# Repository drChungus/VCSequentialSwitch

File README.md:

# Coupled Sequential Switch
#### Double the switches, double the fun!

The Coupled Sequential Switch (CSS) provides two related sequential switches with four steps.

### Specification:
Width:&nbsp;**4 HP**
Depth:&nbsp;**30 mm**
+12V : **5 mA**
-12V: **0 mA**
5V: **0 mA**

A sequential switch is a device to route your signals to different places. The routing can be controlled with a clock signal or a button on the front panel. A reset input is also available to set the switch to its initial routing. This module combines two switches in a small footprint. The signal paths of the two switches are independent, but their state will always be the same. They can be advanced and reset with the same clock signal resulting in a coupled behavior. 
As both switches are always on the same stage this module is ideal to route dual signals, like stereo audio, CV/Gate pairs, and in general vary two independent signals at the same time. Inputs and outputs for the signal path can be switched up!

For more explanation why a sequential switch might be useful in your rack see [mylarmelodies' video](https://www.youtube.com/watch?v=QbxaWluHXEU) on the topic!

##### Inputs:
- Step
- Reset

##### Bipolar:
- 1x I/O
- 4x O/I

##### UI:
- 4x LEDs to indicate the current stage
- Button to advance stage
- Switch to define the number of stages (4, 3 or 2)

NOTE: there might be some reported issues with the current state of the module. Always see [Issues](https://github.com/drChungus/VCSequentialSwitch/issues) reported!

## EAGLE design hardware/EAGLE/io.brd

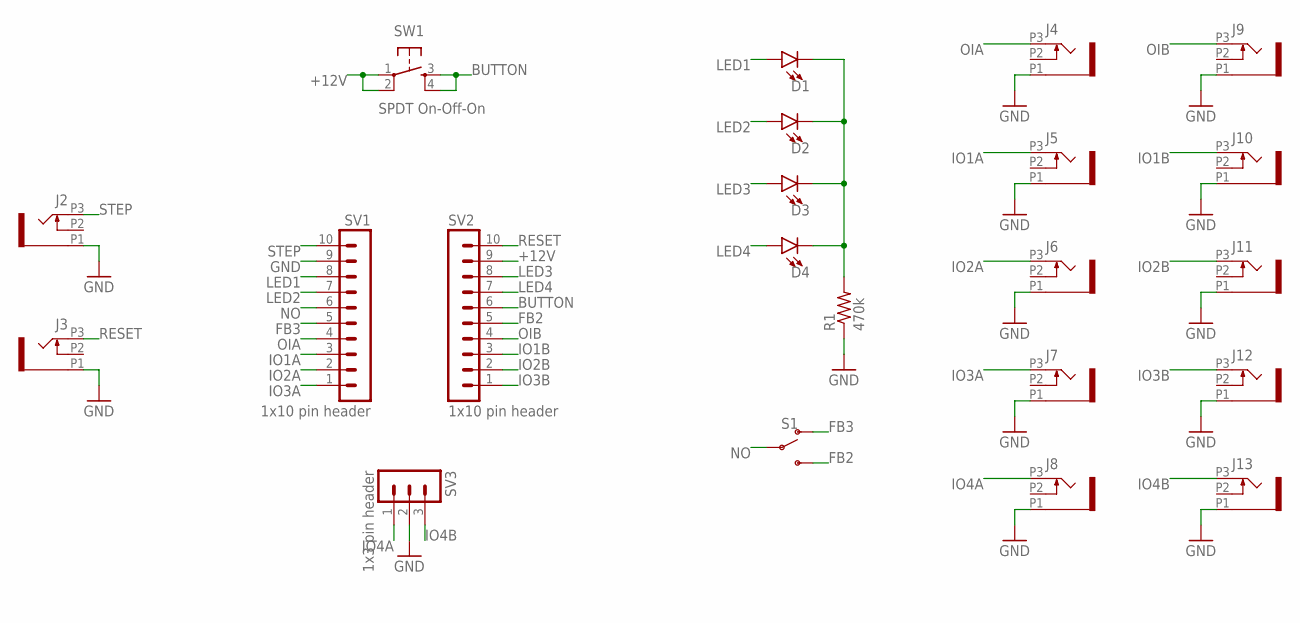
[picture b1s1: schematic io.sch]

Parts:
D1, D2, D3, D4: LED3MM; LED_3MM
J2, J3, J4, J5, J6, J7, J8, J9, J10, J11, J12, J13: PJ301_THONKICONN6; WQP_PJ_301M6
R1: 470k; R0603
S1: SWITCH-SPDT-PTH-11.6X4.0MM-SHORT_LEADS; SWITCH_SPDT_PTH_11.6X4.0MM
SV1, SV2: 1x10 pin header; MA10-1
SV3: 1x3 pin header; MA03-1
SW1: SPDT On-Off-On; TACTILE-PTH

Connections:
+12V: SV2.9, SW1.1, SW1.2
BUTTON: SV2.6, SW1.3, SW1.4
FB2: S1.3 (S), SV2.5
FB3: S1.1 (O), SV1.5
GND: J2.P1 (1), J3.P1 (1), J4.P1 (1), J5.P1 (1), J6.P1 (1), J7.P1 (1), J8.P1 (1), J9.P1 (1), J10.P1 (1), J11.P1 (1), J12.P1 (1), J13.P1 (1), R1.1, SV1.9, SV3.2
IO1A: J5.P3 (3), SV1.3
IO1B: J10.P3 (3), SV2.3
IO2A: J6.P3 (3), SV1.2
IO2B: J11.P3 (3), SV2.2
IO3A: J7.P3 (3), SV1.1
IO3B: J12.P3 (3), SV2.1
IO4A: J8.P3 (3), SV3.1
IO4B: J13.P3 (3), SV3.3
LED1: D1.A, SV1.8
LED2: D2.A, SV1.7
LED3: D3.A, SV2.8
LED4: D4.A, SV2.7
unnamed: D1.K (C), D2.K (C), D3.K (C), D4.K (C), R1.2
NO: S1.2, SV1.6
OIA: J4.P3 (3), SV1.4
OIB: J9.P3 (3), SV2.4
RESET: J3.P3 (3), SV2.10
STEP: J2.P3 (3), SV1.10

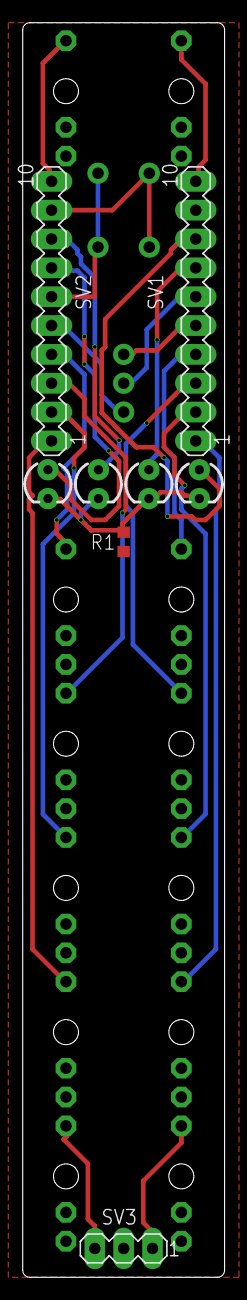
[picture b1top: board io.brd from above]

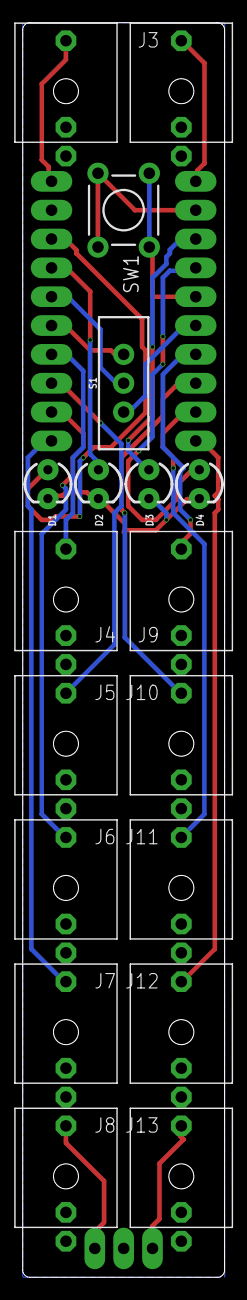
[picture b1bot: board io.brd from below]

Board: 2 copper layers, 17.8 x 110.5 mm, 23 parts (18 on the bottom side), 23 nets.

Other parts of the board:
U$1: EURO_PCB_4HP

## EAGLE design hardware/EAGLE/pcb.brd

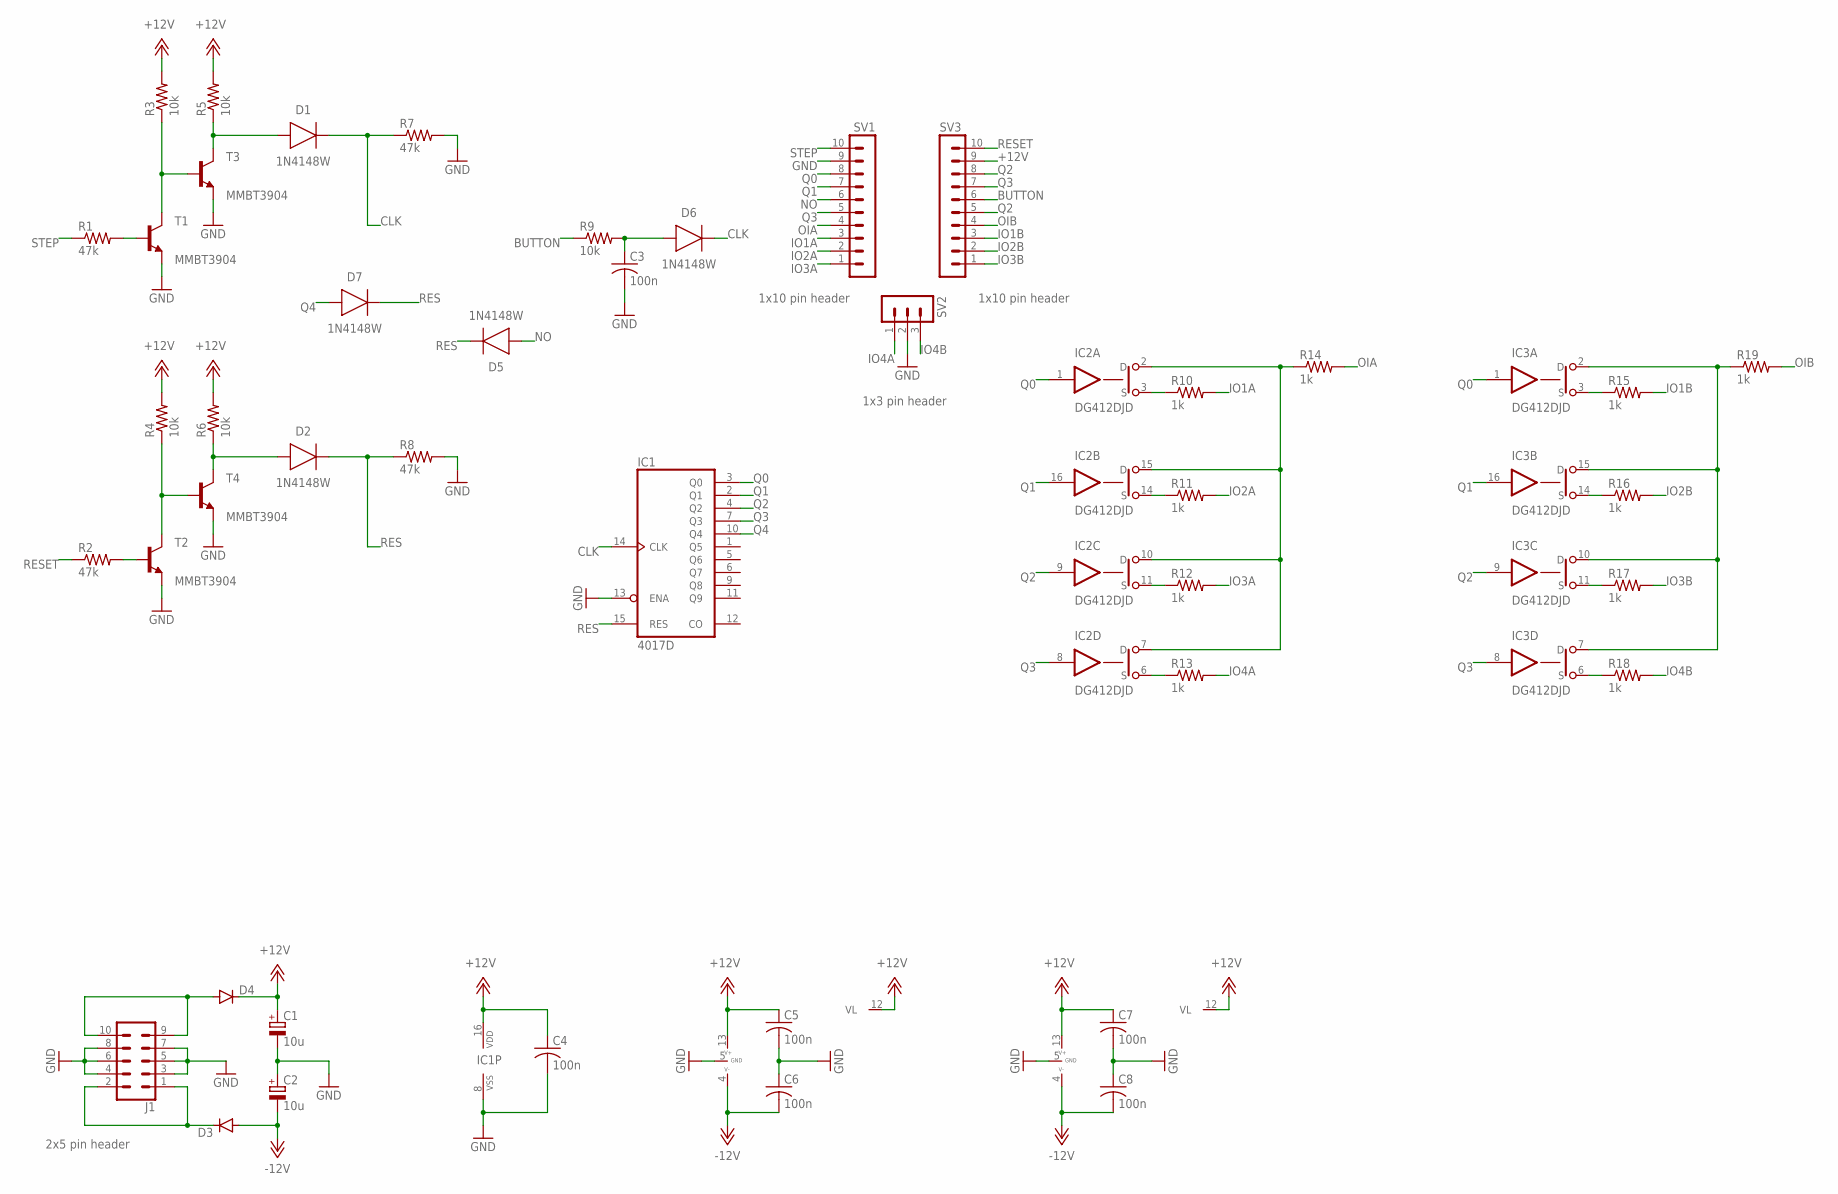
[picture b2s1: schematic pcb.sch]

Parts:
C1, C2: 10u; 153CLV-0605
C3, C4, C5, C6, C7, C8: 100n; C0603
D1, D2, D5, D6, D7: 1N4148W; SOD3715X135
D3, D4: DIODE-SOD123; SOD123
IC1: 4017D; SO16
IC2, IC3: DG412DJD; SO16
J1: 2x5 pin header; 2X5-SHROUDED
R1, R2, R7, R8: 47k; R0603
R3, R4, R5, R6, R9: 10k; R0603
R10, R11, R12, R13, R14, R15, R16, R17, R18, R19: 1k; R0603
SV1, SV3: 1x10 pin header; MA10-1
SV2: 1x3 pin header; MA03-1
T1, T2, T3, T4: MMBT3904; SOT23-BEC

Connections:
+12V: C1.+, C4.1, C5.1, C7.1, D4.C, IC1.16 (VDD), IC2.12 (VL), IC2.13 (V+), IC3.12 (VL), IC3.13 (V+), R3.2, R4.2, R5.2, R6.2, SV3.9
-12V: C2.-, C6.2, C8.2, D3.A, IC2.4 (V-), IC3.4 (V-)
BUTTON: R9.1, SV3.6
CLK: D1.1 (C), D6.1 (C), IC1.14 (CLK), R7.1
GND: C1.-, C2.+, C3.2, C4.2, C5.2, C6.1, C7.2, C8.1, IC1.8 (VSS), IC1.13 (ENA), IC2.5 (GND), IC3.5 (GND), J1.3, J1.4, J1.5, J1.6, J1.7, J1.8, R7.2, R8.2, SV1.9, SV2.2, T1.E, T2.E, T3.E, T4.E
IO1A: R10.2, SV1.3
IO1B: R15.2, SV3.3
IO2A: R11.2, SV1.2
IO2B: R16.2, SV3.2
IO3A: R12.2, SV1.1
IO3B: R17.2, SV3.1
IO4A: R13.2, SV2.1
IO4B: R18.2, SV2.3
unnamed: D4.A, J1.9, J1.10
unnamed: D3.C, J1.1, J1.2
unnamed: IC2.2 (D), IC2.7 (D), IC2.10 (D), IC2.15 (D), R14.1
unnamed: IC2.3 (S), R10.1
unnamed: IC3.2 (D), IC3.7 (D), IC3.10 (D), IC3.15 (D), R19.1
unnamed: IC2.14 (S), R11.1
unnamed: IC2.11 (S), R12.1
unnamed: IC2.6 (S), R13.1
unnamed: IC3.3 (S), R15.1
unnamed: IC3.14 (S), R16.1
unnamed: IC3.11 (S), R17.1
unnamed: IC3.6 (S), R18.1
unnamed: C3.1, D6.2 (A), R9.2
unnamed: R1.2, T1.B
unnamed: R3.1, T1.C, T3.B
unnamed: D1.2 (A), R5.1, T3.C
unnamed: R2.2, T2.B
unnamed: R4.1, T2.C, T4.B
unnamed: D2.2 (A), R6.1, T4.C
NO: D5.2 (A), SV1.6
OIA: R14.2, SV1.4
OIB: R19.2, SV3.4
Q0: IC1.3 (Q0), IC2.1 (IN), IC3.1 (IN), SV1.8
Q1: IC1.2 (Q1), IC2.16 (IN), IC3.16 (IN), SV1.7
Q2: IC1.4 (Q2), IC2.9 (IN), IC3.9 (IN), SV3.5, SV3.8
Q3: IC1.7 (Q3), IC2.8 (IN), IC3.8 (IN), SV1.5, SV3.7
Q4: D7.2 (A), IC1.10 (Q4)
RES: D2.1 (C), D5.1 (C), D7.1 (C), IC1.15 (RES), R8.1
RESET: R2.1, SV3.10
STEP: R1.1, SV1.10

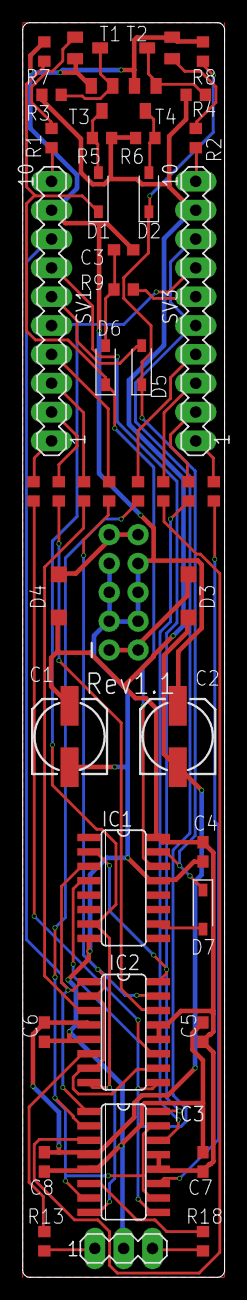
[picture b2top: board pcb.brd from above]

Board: 2 copper layers, 17.8 x 110.5 mm, 46 parts (1 on the bottom side), 43 nets.

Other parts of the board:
U$1: EURO_PCB_4HP

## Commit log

2021-01-04 Initial Commit
    Uploading schematic and .fzz file.
    Circuitry is verified (more or less). Started working on footprints.
2021-01-04 Update SequencialSwitch.fzz
    Updated footprints.
2021-01-04 Update SequencialSwitch.fzz
    arranged jack positions - in theory, needs verification
2021-01-04 Update SequencialSwitch.fzz
    Top and Bottom layer adjustments
2021-01-04 Update SequencialSwitch.fzz
    Top and Bottom switched, external parts locked
2021-01-05 Messing with footprint
2021-01-05 Update SequencialSwitch.fzz
    Locked FP related parts
2021-01-05 Update SequencialSwitch.fzz
    added layout, added holes
2021-01-05 Layout started
    And panel added
2021-01-05 Update SequencialSwitch.fzz
    added new part numbers and footprints :(
2021-01-05 Removed Reset Button, added Reset Switch
    Also reorganized layout
2021-01-05 Started Routing
2021-01-06 Increased PCB size
    20mm is the minimal required pcb size, thus it was enlarged. Also continued routing.
2021-01-06 First Gerber
    Generated first gerber file
2021-01-06 Update SequencialSwitch.fzz
    removed step button
2021-01-06 Routing..
    Routing Baby!
2021-01-06 Update SequencialSwitch.fzz
    routing almost done
2021-01-06 Update SequencialSwitch.fzz
    super Fine!
2021-01-07 Routing Completed
2021-01-07 Panel Outline Done
2021-01-07 Panel design added
2021-01-07 Update panel.fzz
    Added mounting holes and text
2021-01-07 CAM prep
    Created manufacturing files. Jlc has some troubles understanding the pnp
2021-01-08 DESIGN FREEZE
    Successfully converted pnp file, after final inspection should be ready for manufacturing
2021-01-08 Locked PCB
    And fixed some minor layout issues. PCB is ready.
2021-01-08 wORKING ON pANEL dESIGN
2021-01-11 Added 1st iteration art
2021-01-27 Started EAGLE version of design
    Using components already in personal stash
2021-01-27 Eagle design finished
2021-01-27 eagle
2021-01-27 FINALIZED PCBs
2021-01-27 gerbers with some errors
    gnd pane on pcb
2021-01-27 Submitted for Artist
    and quick fixed layer errors
2021-01-28 Added text and logo
2021-01-28 6mm Switch hole
    6
2021-01-31 Added BOM
    And buffer caps, and refined design
2021-01-31 Added Panel BMP
    with the command 2 export
2021-01-31 Updated BOM with personal stash info
2021-02-19 Art
    Added art
2021-02-19 graphics
2021-02-22 finalized Panel
    ready for production
2021-02-23 panel
    noPanel
2021-02-23 uppedMerger
    Still not working
2021-05-06 Looking at documentation for build
2021-05-07 new images!
    added images
2021-05-07 New Images lol
2021-05-26 Images added and removed
2021-06-06 Added Photoshooting Images
2021-06-07 Transistor footprint fixed
2021-06-22 Fixed some layout issues
2021-06-22 Added smd 4017 footprint
2021-07-28 Deleted Temp files
2021-09-09 Update sequentialSwitch_bom.xlsx
    Fixed a wrong reference to the DG412 in the manufacturing (PNP) file.

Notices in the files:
parts and their libraries:
SparkFun-LED: Licensing: Creative Commons ShareAlike 4.0 International - https://creativecommons.org/licenses/by-sa/4.0
